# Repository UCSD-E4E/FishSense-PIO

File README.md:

- Purpose of board is to limit inrush current to orbitty 
- trace cut between gate of Q3 NMOS and bottom of R11
- 50k connected to bottom of gate of Q3
- connect bottom of 1 uF(>= 100 nF should suffice) cap to ground of RV1
- Wire from bottom of R11 to bottom of 50k at gate of Q3
- Additional wire from bottom of Q3 50k to top of cop
- Check that 50k resistance exists between gate of Q2 and drain of Q3
- Do not include RV1, R9, R10
- Voltage threshold across R4 should be 9.5-10V upon start

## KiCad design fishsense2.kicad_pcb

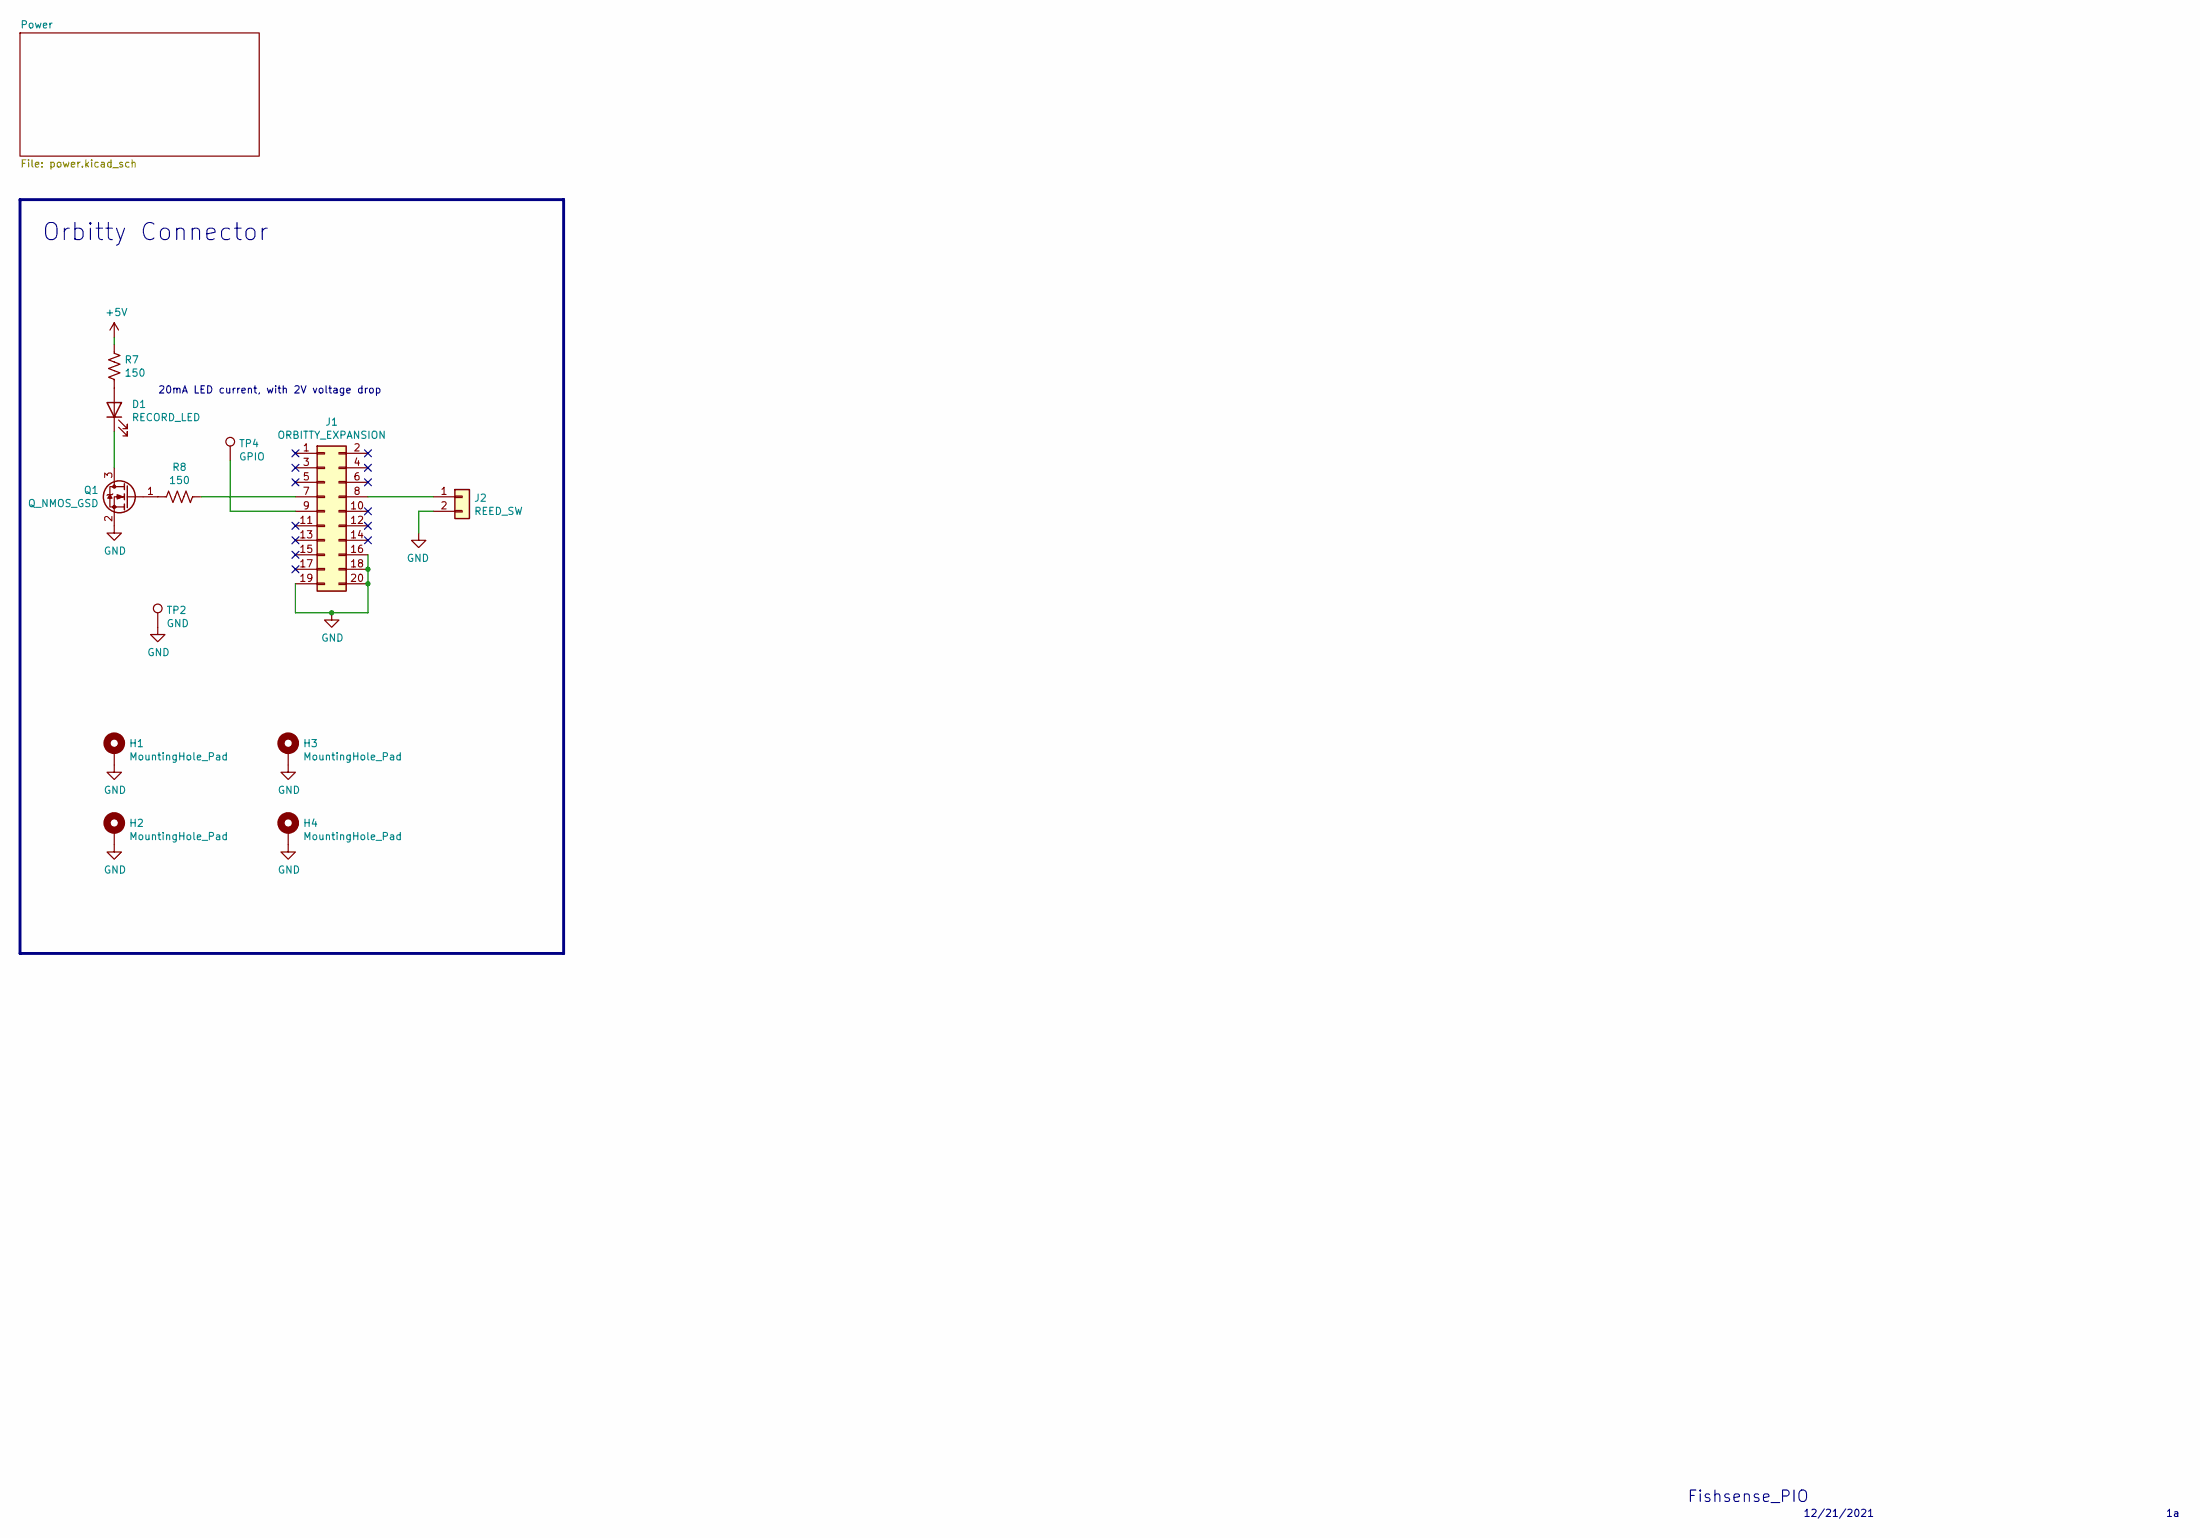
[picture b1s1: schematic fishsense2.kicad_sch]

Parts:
D1: RECORD_LED; LED_D5.0mm_FlatTop
H1, H2, H3, H4: MountingHole_Pad; MountingHole_2.7mm_M2.5_Pad
J1: ORBITTY_EXPANSION; PinSocket_2x10_P2.54mm_Vertical
J2: REED_SW; JST_XH_S2B-XH-A_1x02_P2.50mm_Horizontal
Q1: Q_NMOS_GSD; SOT-23_Handsoldering
R7, R8: 150; R_1206_3216Metric_Pad1.30x1.75mm_HandSolder
TP2: GND; TestPoint_Plated_Hole_D2.0mm
TP4: GPIO; TestPoint_Plated_Hole_D2.0mm

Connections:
+5V: R7.1; also elsewhere on the board
GND: H1.1, H2.1, H3.1, H4.1, J1.16, J1.18, J1.19, J1.20, J2.2, Q1.2 (S), TP2.1; also elsewhere on the board
unnamed: D1.1 (K), Q1.3 (D)
unnamed: D1.2 (A), R7.2
unnamed: J1.7, R8.1
unnamed: J1.8, J2.1
unnamed: J1.9, TP4.1
unnamed: Q1.1 (G), R8.2

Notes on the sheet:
20mA LED current, with 2V voltage drop
12/21/2021
Orbitty Connector
Fishsense_PIO

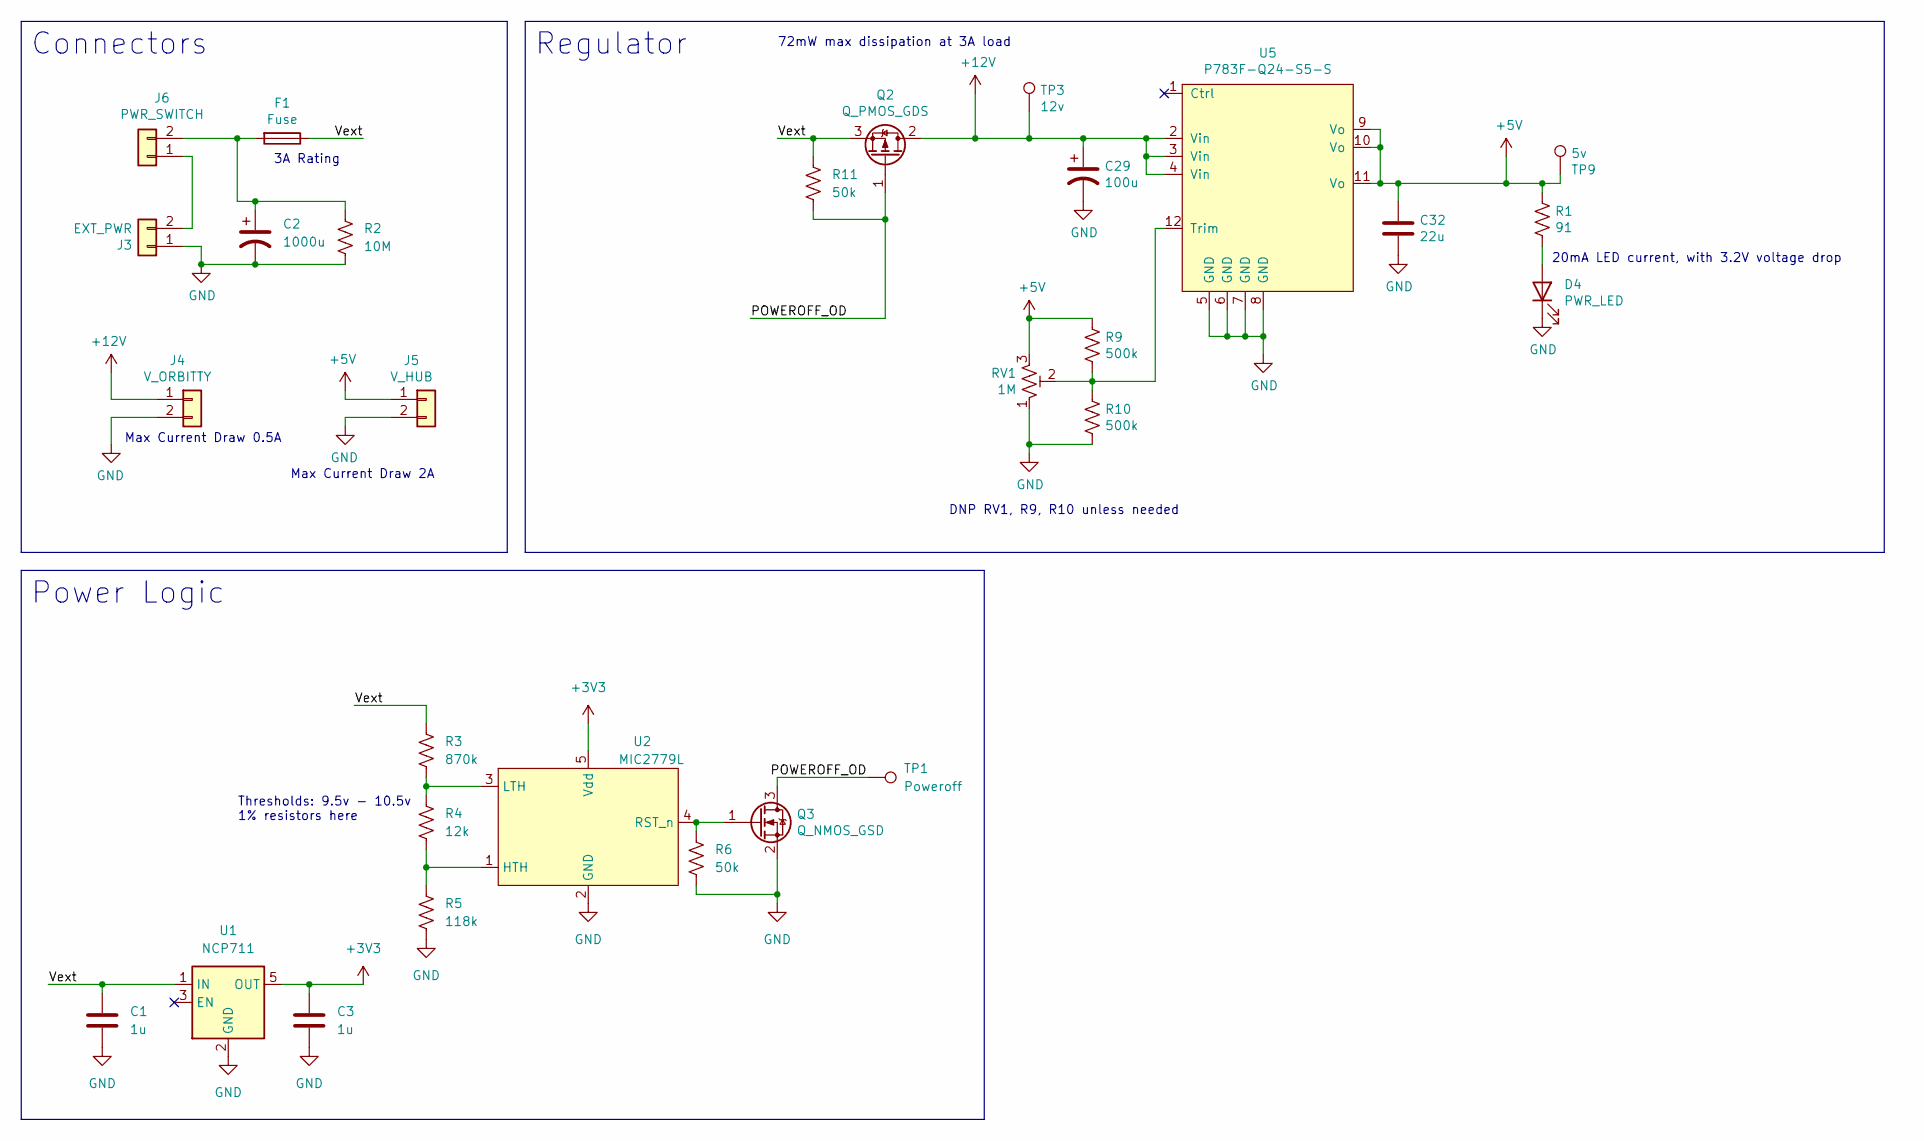
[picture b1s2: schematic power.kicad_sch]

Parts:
C1, C3: 1u; C_1206_3216Metric_Pad1.33x1.80mm_HandSolder
C2: 1000u; CP_Axial_L30.0mm_D12.5mm_P35.00mm_Horizontal
C29: 100u; CP_Radial_D8.0mm_P3.50mm
C32: 22u; C_1206_3216Metric_Pad1.33x1.80mm_HandSolder
D4: PWR_LED; LED_D5.0mm_FlatTop
F1: Fuse; Fuseholder_Cylinder-5x20mm_Stelvio-Kontek_PTF78_Horizontal_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
J3: EXT_PWR; AMASS_XT30PW-M_1x02_P2.50mm_Horizontal
J4: V_ORBITTY; JST_XH_S2B-XH-A_1x02_P2.50mm_Horizontal
J5: V_HUB; JST_XH_S2B-XH-A_1x02_P2.50mm_Horizontal
J6: PWR_SWITCH; JST_XH_S2B-XH-A_1x02_P2.50mm_Horizontal
Q2: Q_PMOS_GDS; TO-251-3_Vertical
Q3: Q_NMOS_GSD; SOT-23_Handsoldering
R1: 91; R_1206_3216Metric_Pad1.30x1.75mm_HandSolder
R2: 10M; R_1206_3216Metric_Pad1.30x1.75mm_HandSolder
R3: 870k; R_1206_3216Metric_Pad1.30x1.75mm_HandSolder
R4: 12k; R_1206_3216Metric_Pad1.30x1.75mm_HandSolder
R5: 118k; R_1206_3216Metric_Pad1.30x1.75mm_HandSolder
R6, R11: 50k; R_1206_3216Metric_Pad1.30x1.75mm_HandSolder
R9, R10: 500k; R_1206_3216Metric_Pad1.30x1.75mm_HandSolder
RV1: 1M; Potentiometer_Bourns_3269W_Vertical
TP1: Poweroff; TestPoint_Plated_Hole_D2.0mm
TP3: 12v; TestPoint_Plated_Hole_D2.0mm
TP9: 5v; TestPoint_Plated_Hole_D2.0mm
U1: NCP711; SOT-23-5
U2: MIC2779L; SOT-23-5
U5: P783F-Q24-S5-S; Converter_DCDC_RECOM_R5xxxPA_THT

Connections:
+3V3: C3.1, U1.5 (OUT), U2.5 (Vdd)
+5V: C32.1, J5.1, R1.1, R9.1, RV1.3, TP9.1, U5.9 (Vo), U5.10 (Vo), U5.11 (Vo); also elsewhere on the board
+12V: C29.1, J4.1, Q2.2 (D), TP3.1, U5.2 (Vin), U5.3 (Vin), U5.4 (Vin)
/Power/POWEROFF_OD: Q2.1 (G), Q3.3 (D), R11.2, TP1.1
/Power/Vext: C1.1, F1.1, Q2.3 (S), R3.1, R11.1, U1.1 (IN)
GND: C1.2, C2.2, C3.2, C29.2, C32.2, D4.1 (K), J3.1, J4.2, J5.2, Q3.2 (S), R2.2, R5.2, R6.2, R10.2, RV1.1, U1.2 (GND), U2.2 (GND), U5.5 (GND), U5.6 (GND), U5.7 (GND), U5.8 (GND); also elsewhere on the board
unnamed: C2.1, F1.2, J6.2, R2.1
unnamed: D4.2 (A), R1.2
unnamed: J3.2, J6.1
unnamed: Q3.1 (G), R6.1, U2.4 (RST_n)
unnamed: R3.2, R4.1, U2.3 (LTH)
unnamed: R4.2, R5.1, U2.1 (HTH)
unnamed: R9.2, R10.1, RV1.2, U5.12 (Trim)

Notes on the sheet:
DNP RV1, R9, R10 unless needed
Thresholds: 9.5v - 10.5v 1% resistors here
Regulator
Max Current Draw 0.5A
Connectors
3A Rating
Power Logic
20mA LED current, with 3.2V voltage drop
Max Current Draw 2A
72mW max dissipation at 3A load

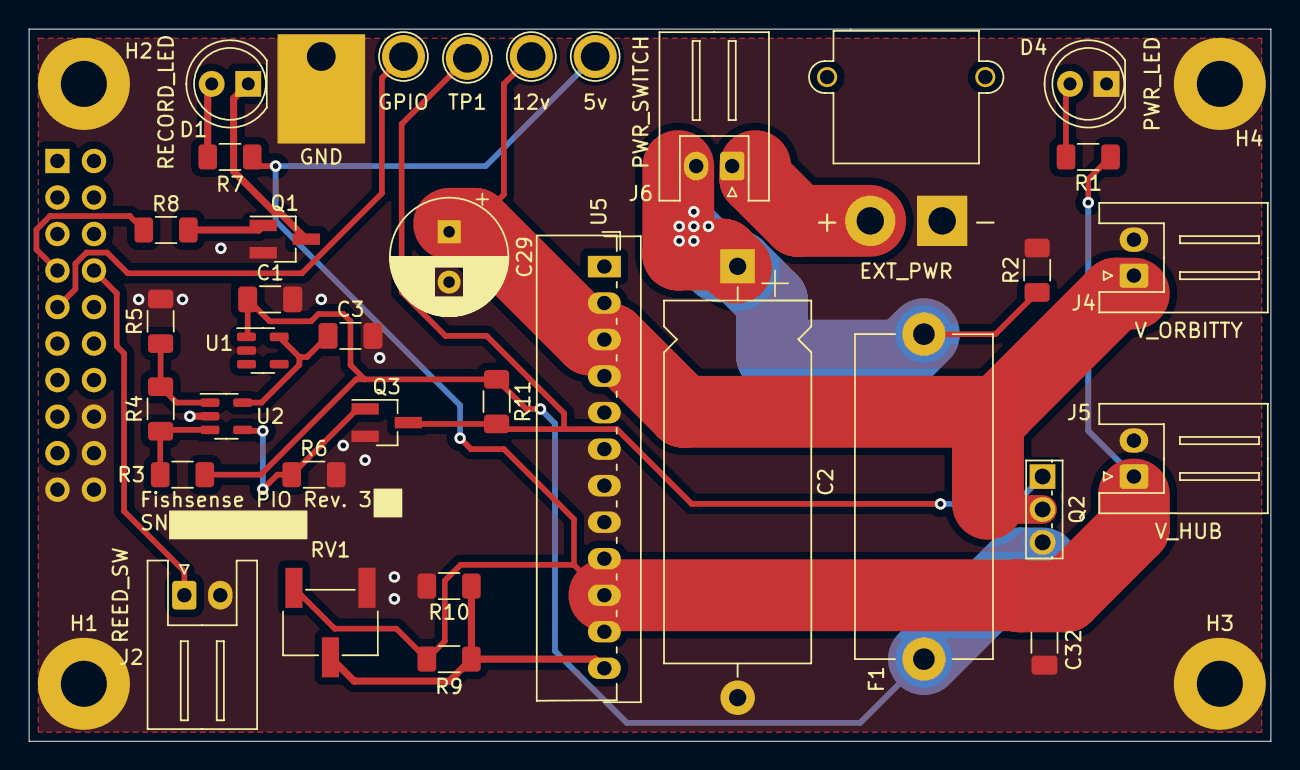
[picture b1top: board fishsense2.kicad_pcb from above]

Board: 2 copper layers, 86.4 x 49.5 mm, 41 parts (1 on the bottom side), 19 nets.

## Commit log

2021-10-12 General PCB layout and major part choices.
2021-10-18 Added symbols and footprints. More space for connectors on PCB.
2021-10-26 Finished schematic. Added all footprints. Arranged components and routed differential signals.
2021-11-07 Small fixes to schematic.
2021-11-07 Updated footprints. Placed components and added silkscreen.
2021-11-08 Changed footprints to right angle versions. Adjusted board outline to orbitty carrier size.
2021-11-08 Added battery undervoltage protection, needs consideration as to whether it would work.
2021-11-12 Removed uneeded DC barrel power. Adjusted component values for 12v supply. Checked footprints.
2021-11-13 Moved components around on PCB. Fixed fuse footprint.
2021-11-13 Routed traces.
2021-12-08 Revised for BlueRobotics switch.
2021-12-08 Routed Traces
2021-12-08 Added load switch
2021-12-08 Some footprint and part changes based on availability.
2021-12-12 Replaced tps3711 with different part which is in stock.
2021-12-15 Swapped tps3711 for tl7702b because of availability. Added extra hysteresis to voltage supervisor.
2021-12-22 Many changes from first design review.
2021-12-22 Added logo to PCB. Changed resistance to preferred value.
2022-02-11 Possible revision without feedback. Changes on schematic but not PCB.
2022-04-16 Rev 3 Changes
2022-04-16 Some footprint fixes.
2022-04-17 Small fixes.
2022-04-20 Changed to axial capacitor, fixed mounting hole size.
2022-05-04 Latest rev 3
2022-07-14 Updated gitignore
